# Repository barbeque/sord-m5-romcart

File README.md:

# Current status
*** NOT WORKING ***

# Thanks to
 - [hardyboy blog post](http://blog.livedoor.jp/hardyboy/archives/10225772.html)
 - [mm references](http://www.retropc.net/mm/m5/)

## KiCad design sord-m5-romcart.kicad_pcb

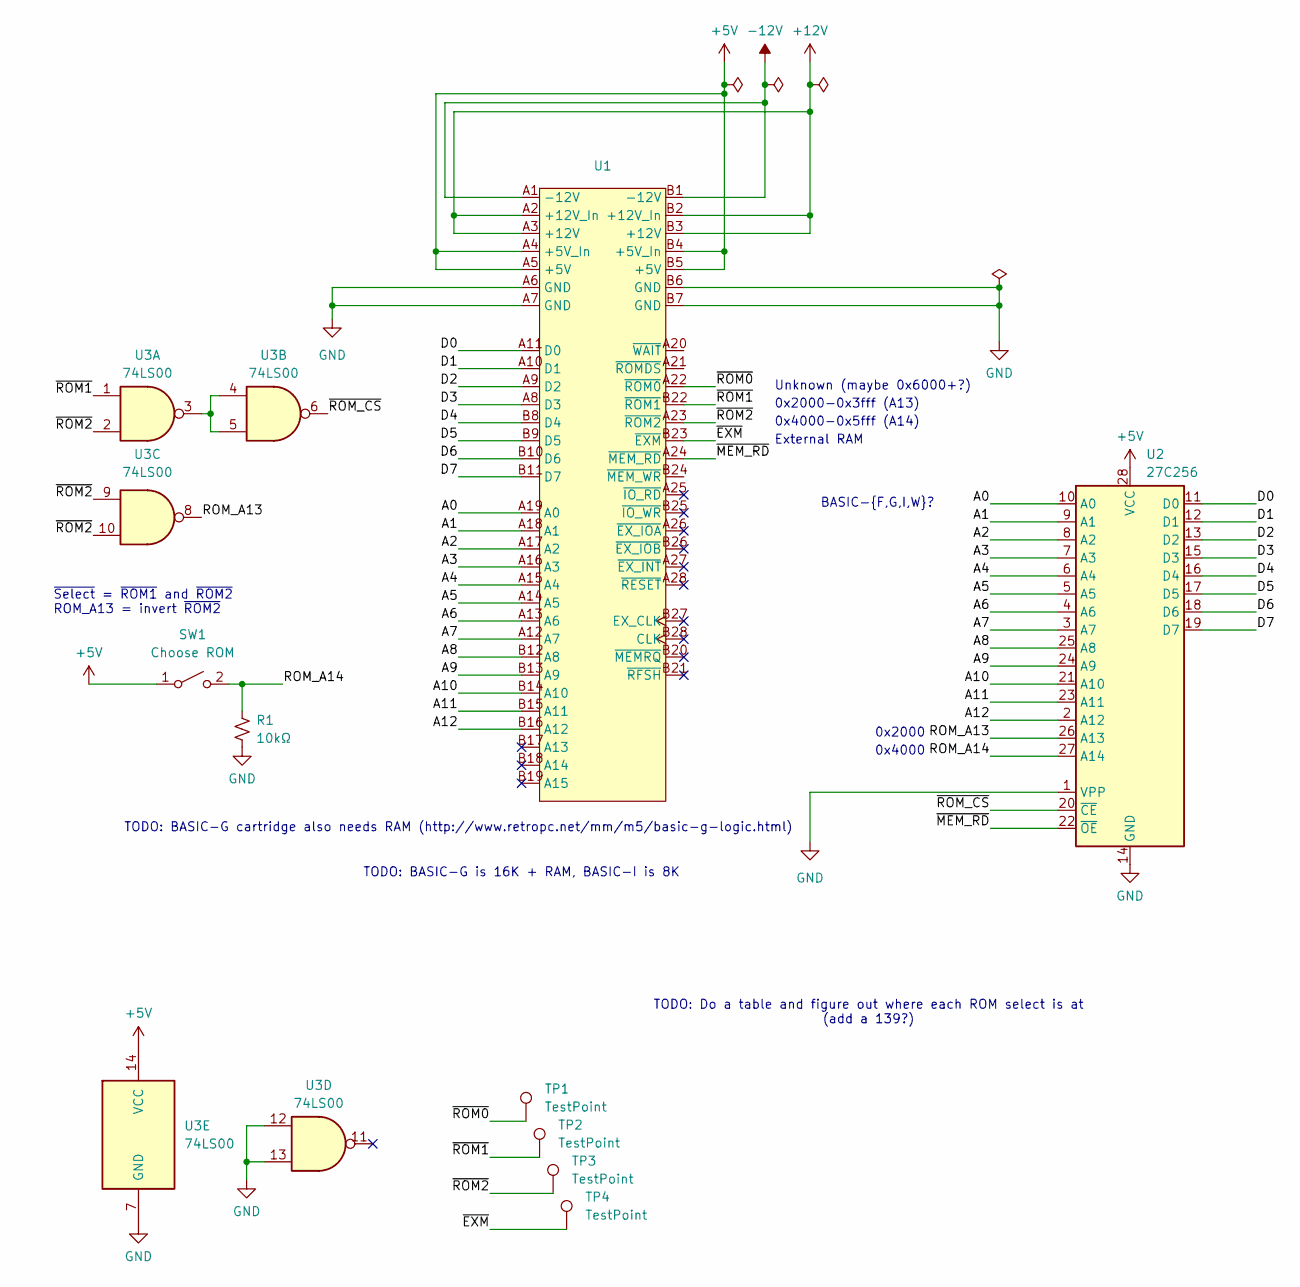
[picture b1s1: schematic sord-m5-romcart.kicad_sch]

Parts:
R1: 10kΩ; R_Axial_DIN0207_L6.3mm_D2.5mm_P10.16mm_Horizontal
SW1: Choose ROM; PinHeader_1x02_P2.54mm_Vertical
TP1, TP2, TP3, TP4: TestPoint; TestPoint_Loop_D1.80mm_Drill1.0mm_Beaded
U1: M5_CartridgeSlot
U2: 27C256; DIP-28_W15.24mm_Socket_LongPads
U3: 74LS00; DIP-14_W7.62mm_Socket_LongPads

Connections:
+5V: SW1.1 (A), U1.A4 (+5V_In), U1.A5 (+5V), U1.B4 (+5V_In), U1.B5 (+5V), U2.28 (VCC), U3.14 (VCC)
+12V: U1.A2 (+12V_In), U1.A3 (+12V), U1.B2 (+12V_In), U1.B3 (+12V)
-12V: U1.A1 (-12V), U1.B1 (-12V)
/A0: U1.A19 (A0), U2.10 (A0)
/A1: U1.A18 (A1), U2.9 (A1)
/A2: U1.A17 (A2), U2.8 (A2)
/A3: U1.A16 (A3), U2.7 (A3)
/A4: U1.A15 (A4), U2.6 (A4)
/A5: U1.A14 (A5), U2.5 (A5)
/A6: U1.A13 (A6), U2.4 (A6)
/A7: U1.A12 (A7), U2.3 (A7)
/A8: U1.B12 (A8), U2.25 (A8)
/A9: U1.B13 (A9), U2.24 (A9)
/A10: U1.B14 (A10), U2.21 (A10)
/A11: U1.B15 (A11), U2.23 (A11)
/A12: U1.B16 (A12), U2.2 (A12)
/D0: U1.A11 (D0), U2.11 (D0)
/D1: U1.A10 (D1), U2.12 (D1)
/D2: U1.A9 (D2), U2.13 (D2)
/D3: U1.A8 (D3), U2.15 (D3)
/D4: U1.B8 (D4), U2.16 (D4)
/D5: U1.B9 (D5), U2.17 (D5)
/D6: U1.B10 (D6), U2.18 (D6)
/D7: U1.B11 (D7), U2.19 (D7)
/ROM_A13: U2.26 (A13), U3.8
/ROM_A14: R1.1, SW1.2 (B), U2.27 (A14)
/~EXM: TP4.1, U1.B23 (~EXM)
/~MEM_RD: U1.A24 (~MEM_RD), U2.22 (~OE)
/~ROM0: TP1.1, U1.A22 (~ROM0)
/~ROM1: TP2.1, U1.B22 (~ROM1), U3.1
/~ROM2: TP3.1, U1.A23 (~ROM2), U3.2, U3.9, U3.10
/~ROM_CS: U2.20 (~CE), U3.6
GND: R1.2, U1.A6 (GND), U1.A7 (GND), U1.B6 (GND), U1.B7 (GND), U2.1 (VPP), U2.14 (GND), U3.7 (GND), U3.12, U3.13
unnamed: U3.3, U3.4, U3.5

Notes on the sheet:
TODO: BASIC-G is 16K + RAM, BASIC-I is 8K
0x2000-0x3fff (A13)
0x2000
TODO: Do a table and figure out where each ROM select is at (add a 139?)
~{Select} = ~{ROM1} and ~{ROM2} ROM_A13 = invert ~{ROM2}
0x4000-0x5fff (A14)
Unknown (maybe 0x6000+?)
BASIC-{F,G,I,W}?
TODO: BASIC-G cartridge also needs RAM (http://www.retropc.net/mm/m5/basic-g-logic.html)
External RAM
0x4000

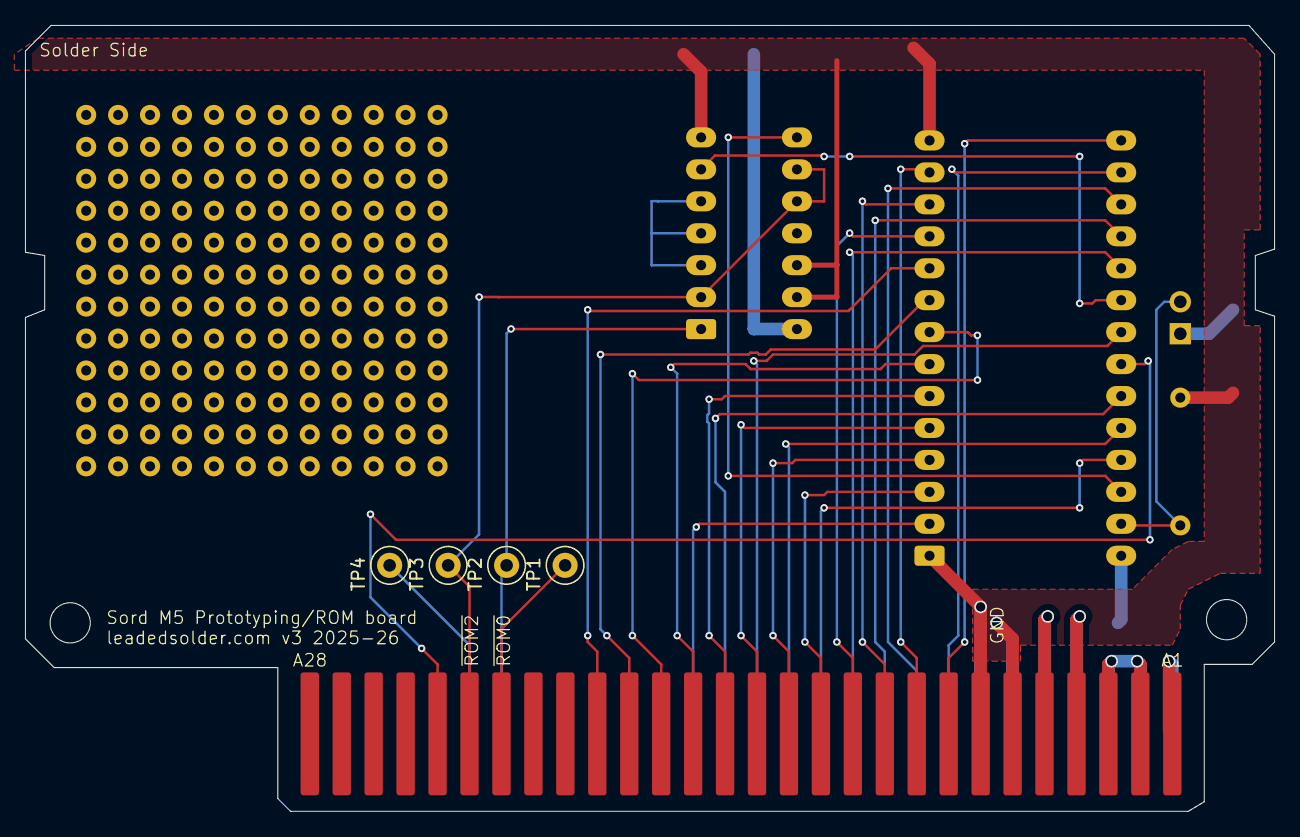
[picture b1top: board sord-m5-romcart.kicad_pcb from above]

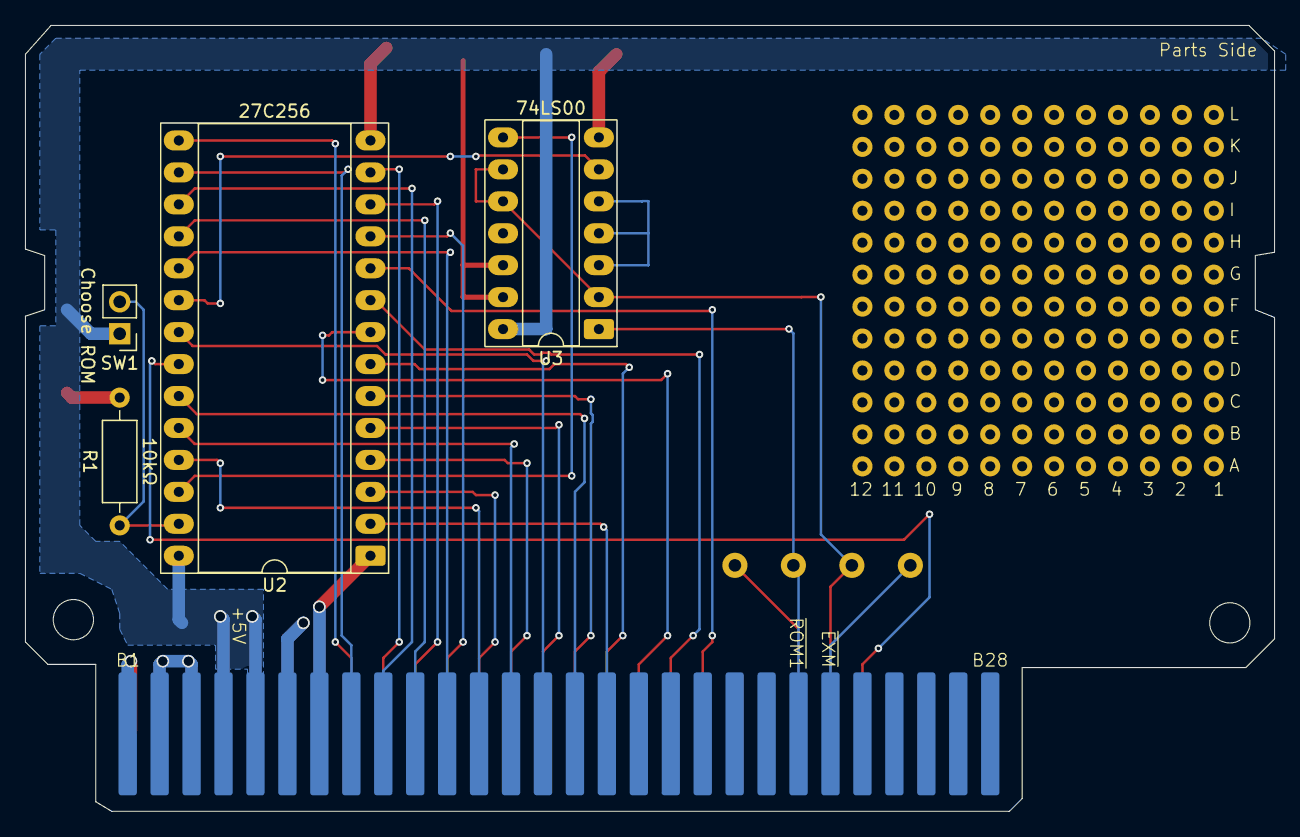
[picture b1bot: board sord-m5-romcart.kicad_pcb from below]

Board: 2 copper layers, 99.3 x 62.5 mm, 9 parts (4 on the bottom side), 34 nets.

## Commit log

2025-01-27 Symbol created
2025-01-27 Investigating banking
2025-01-27 Add banks B, C
2025-01-27 New feature for decody
2025-01-27 memory map link
2025-01-27 Fumbling
2025-01-27 A12 restored
2025-01-27 Updated decode
2025-02-27 Rough cartridge edge
2025-02-27 Board outline
2025-02-27 Symbol cleanout
2025-02-27 Significant symbol mess
2025-02-27 Version numbers
2025-02-27 V1 sent to fab
2025-02-28 Use hole footprints for the sake of TurboCase later
2025-03-20 Cleaning up little things
2026-06-23 Converted to ROM1 base, re-routed
2026-06-23 Sent to fab
2026-06-24 Use AND not NAND
2026-06-24 Revert "Use AND not NAND"
    This reverts commit 911c91f3a1e7fcb4d358834b32dfa7806c5ac1fb.
2026-06-30 Add tooth labels
